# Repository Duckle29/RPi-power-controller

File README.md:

# RPi-power-controller

The RPi-power-controller is a small, ATTiny85 based power controller,
that talks to a RPi over software serial, via the hardware serial port,
and issues a shutdown command.

There are plans to support custom commands, by sending the desired command to
the board from the rpi.

The board also features two 10A SPDT relays, intended to be used to break both live and neutral, to safely handle schuko style plugs, but could be used in parallel to handle larger loads.

TODO:
* BOM
* Firmware

### Images
Here's some renders of the board to be

[PCB-top]: https://644db4de3505c40a0444-327723bce298e3ff5813fb42baeefbaa.ssl.cf1.rackcdn.com/1f80f6248889095e2f93bf03f451f997.png "Top side of the PCB"
[PCB-bot]: https://644db4de3505c40a0444-327723bce298e3ff5813fb42baeefbaa.ssl.cf1.rackcdn.com/245595cf08f88fd80672bb5110447598.png "Bottom side of the PCB"

![PCB top side][PCB-top]
![PCB bottom side][PCB-bot]

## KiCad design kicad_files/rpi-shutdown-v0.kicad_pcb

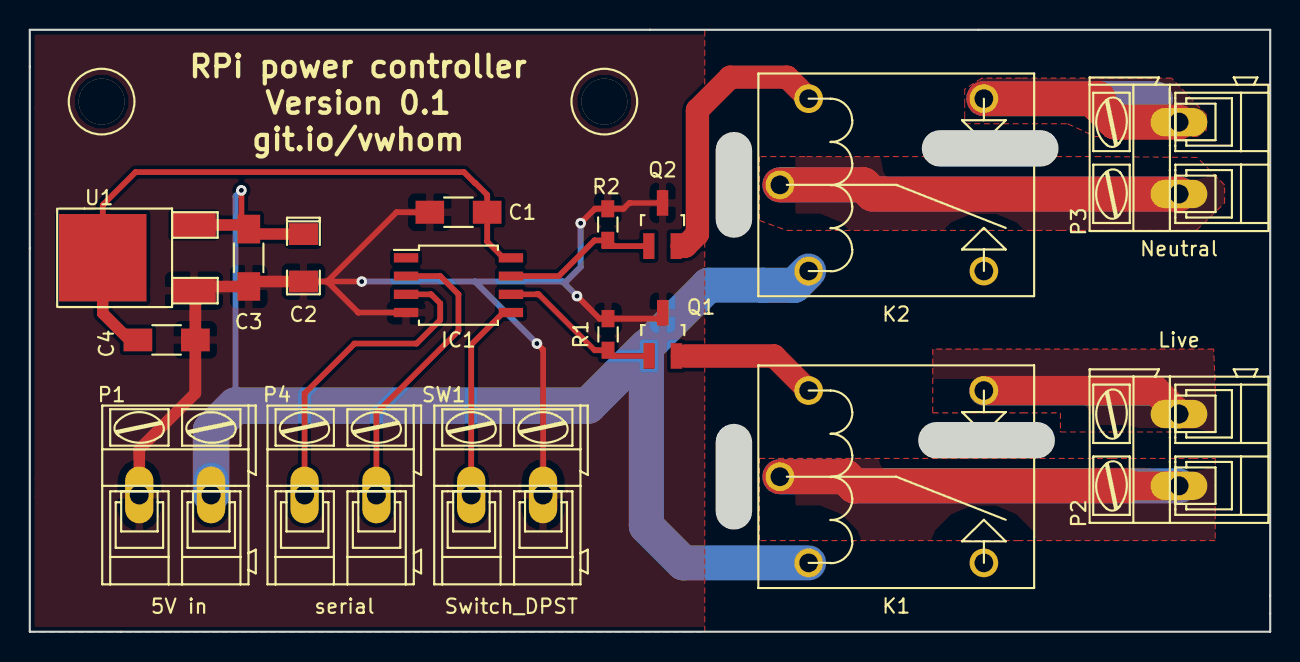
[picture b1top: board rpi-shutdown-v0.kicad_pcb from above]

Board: 2 copper layers, 84.0 x 39.5 mm, 17 parts (0 on the bottom side), 14 nets.

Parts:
C1, C3, C4: 100nF; C_1206_HandSoldering
C2: 10uF; SMD-1206_Pol
IC1: ATTINY85-S; SOIJ-8_5.3x5.3mm_Pitch1.27mm
K1, K2: Relay_SPDT; ORWH-SH-105D1F,000
P1: 5V in; AK300-2
P2: Live; AK300-2
P3: Neutral; AK300-2
P4: serial; AK300-2
Q1, Q2: FDN339AN; SOT-23_Handsoldering
R1, R2: 10k; R_0603_HandSoldering
SW1: Switch_DPST; AK300-2
U1: AP1117D33; TO-252-2Lead

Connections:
+3V3: C1.1, C4.1, IC1.8, U1.2
+5V: C2.1, C3.1, K1.1, K2.1, P1.2, U1.3
/relays/CH:1: IC1.6, Q1.1, R1.1
/relays/CH:2: IC1.7, Q2.1, R2.1
GND: C1.2, C2.2, C3.2, C4.2, IC1.4, P1.1, Q1.3, Q2.3, R1.2, R2.2, SW1.2, U1.1
unnamed: IC1.2, P4.2
unnamed: IC1.3, P4.1
unnamed: IC1.5, SW1.1
unnamed: K1.2, Q1.2
unnamed: K1.3, P2.1
unnamed: K1.5, P2.2
unnamed: K2.2, Q2.2
unnamed: K2.3, P3.1
unnamed: K2.5, P3.2

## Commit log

2016-05-07 Renamed readme
2016-05-07 Put some actual text in readme
2016-05-07 Added gerbers
2016-05-08 Added gerbers and cleaned up silkscreen
2016-05-08 Added renders of the board, and updated the readme a bit
